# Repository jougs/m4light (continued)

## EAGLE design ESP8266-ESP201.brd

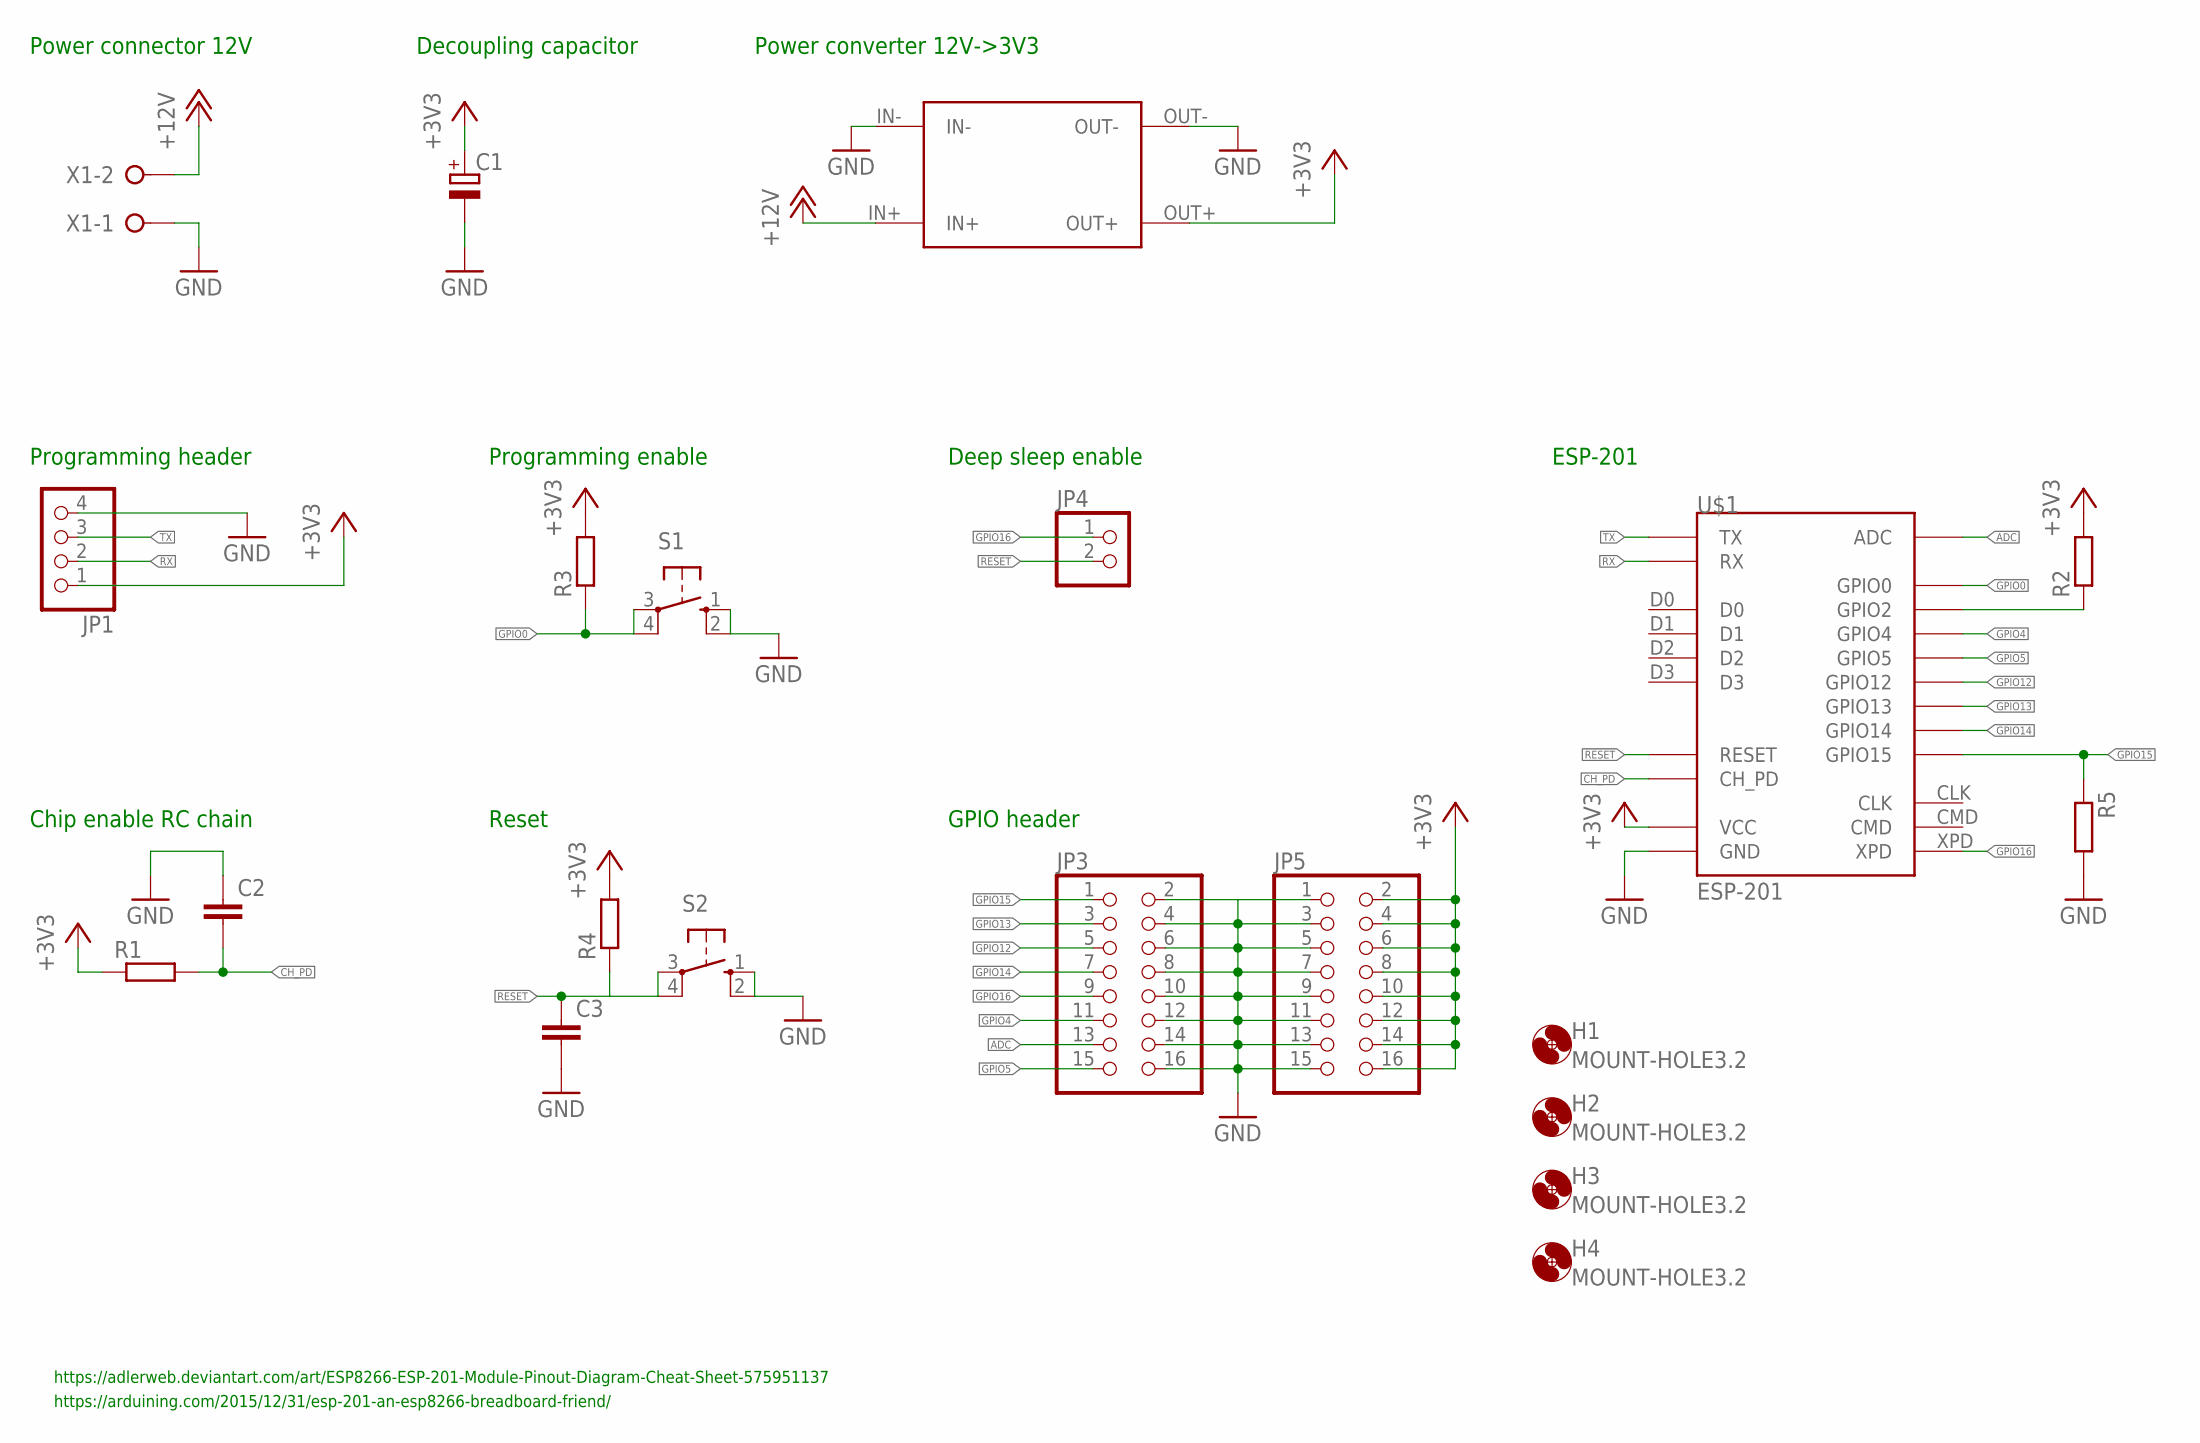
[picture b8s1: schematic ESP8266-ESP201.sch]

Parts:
C1: CPOL-EUE2.5-5; E2,5-5
C2, C3: C-EU025-024X044; C025-024X044
H1, H2, H3, H4: MOUNT-HOLE3.2; 3,2
JP1: PINHD-1X4; 1X04
JP3, JP5: PINHD-2X8; 2X08
JP4: PINHD-1X2; 1X02
R1, R2, R3, R4, R5: R-EU_0207/10; 0207/10
S1, S2: 10-XX; B3F-10XX
U$1: ESP-201
U$2: MINI360
X1: W237-02P; W237-132

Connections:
+3V3: C1.+, JP1.1, JP5.2, JP5.4, JP5.6, JP5.8, JP5.10, JP5.12, JP5.14, JP5.16, R1.1, R2.2, R3.2, R4.2, U$1.3V3 (VCC), U$1.3V3_2 (VCC), U$1.3V3_3 (VCC), U$2.OUT+
+12V: U$2.IN+, X1.2
ADC: JP3.13, U$1.ADC
CH_PD: C2.2, R1.2, U$1.CH_PD
GND: C1.-, C2.1, C3.2, JP1.4, JP3.2, JP3.4, JP3.6, JP3.8, JP3.10, JP3.12, JP3.14, JP3.16, JP5.1, JP5.3, JP5.5, JP5.7, JP5.9, JP5.11, JP5.13, JP5.15, R5.2, S1.1 (S), S1.2 (S1), S2.1 (S), S2.2 (S1), U$1.GND, U$1.GND_2 (GND), U$1.GND_3 (GND), U$2.IN-, U$2.OUT-, X1.1
GPIO0: R3.1, S1.3, S1.4 (P1), U$1.GPIO0
GPIO2: R2.1, U$1.GPIO2
GPIO4: JP3.11, U$1.GPIO4
GPIO5: JP3.15, U$1.GPIO5
GPIO12: JP3.5, U$1.GPIO12
GPIO13: JP3.3, U$1.GPIO13
GPIO14: JP3.7, U$1.GPIO14
GPIO15: JP3.1, R5.1, U$1.GPIO15
GPIO16: JP3.9, JP4.1, U$1.XPD
RESET: C3.1, JP4.2, R4.1, S2.3, S2.4 (P1), U$1.RST (RESET)
RX: JP1.2, U$1.RX
TX: JP1.3, U$1.TX

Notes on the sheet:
Power connector 12V
Power converter 12V->3V3
Decoupling capacitor
Programming header
Chip enable RC chain
Programming enable
ESP-201
GPIO header
Reset
https://adlerweb.deviantart.com/art/ESP8266-ESP-201-Module-Pinout-Diagram-Cheat-Sheet-575951137
https://arduining.com/2015/12/31/esp-201-an-esp8266-breadboard-friend/
Deep sleep enable

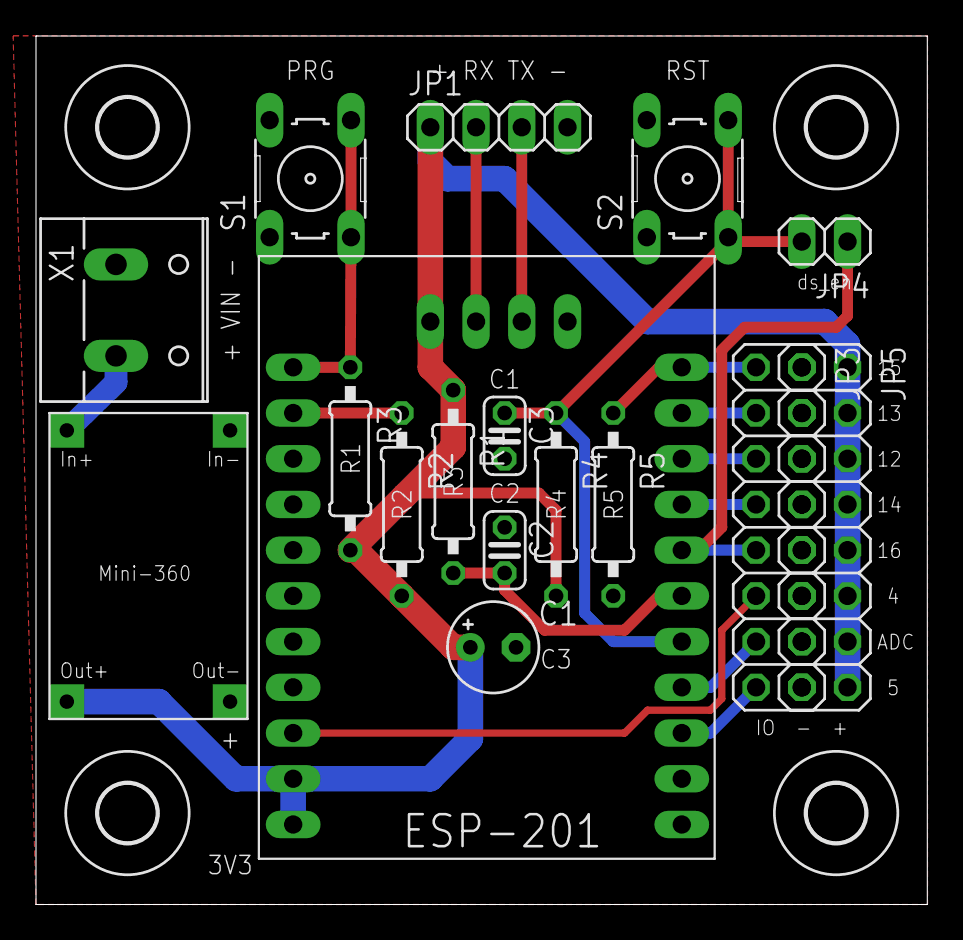
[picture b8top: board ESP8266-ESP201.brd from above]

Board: 2 copper layers, 49.5 x 48.2 mm, 21 parts (0 on the bottom side), 17 nets.

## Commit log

2016-08-13 Power supply board for ESP201
2016-08-13 Power distribution board for courtyard light
2016-08-13 Cable distribution board for courtyard light
2016-08-13 Arduino MINI PRO based light control for boiler room
2016-08-13 RGB strip board with five ports
2016-08-13 Warm white strip board with five ports
2016-09-06 Added basic gitignore file containing eagle backup files
2016-09-06 New version of the board with proper mounting holes and smaller footprint
2016-09-17 Initial version of the mosfet board
2017-01-17 Added second layer with ground plate
2017-01-18 More compact layout and added bottom silk screen
2017-01-18 Added GERBER files for ESP201 board
2017-01-18 Updated and extended descriptions and added bottom silk screen
2017-01-18 Added GERBER files for MOSFET board
2017-01-18 Increased size of 3v3 trace and updated GERBER files
2017-01-28 Removed 3V3 test point
2017-09-13 Adding PWM dimmable constant current source based on Meanwell LDD-H drivers
2017-09-13 Adding ESP-12 board with voltage voltage regulator and 4 GPIOs directly connected to MOSFETs
2017-10-11 Remove unneccessary solder paste layers
2017-10-11 Adding CAMJob that works (at least) for production at EasyEDA
2017-10-12 New version
2017-10-12 Fixed bug in routing of Out- for the constant current modules
2017-10-12 Added and updated GERBER files
2017-10-12 Updated MOSFET board
2018-12-21 Adding pcb design for psu switch board
2019-12-16 Remove pulldown enable jumpers and compact and rotate connectors.
2019-12-16 Add initial version of input/output expander.
2019-12-16 Fix label and add GERBER files for PSU switch.
2019-12-16 Initial version of 8-channel opto-insulated multi-voltage input stage.
2019-12-16 Initial version of shift register based output stage.
2019-12-16 Adding cie1931 generator script
2019-12-16 Update git ignore file
2019-12-16 Nicely working micropython firmware for the light control
2019-12-16 First version of micropython firmware for the input/output stage
